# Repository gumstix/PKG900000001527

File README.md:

# Gumstix Raspberry Pi CM4 PoE Smart Camera
# PKG900000001527 ![][thumbnail]

The **Gumstix Raspberry Pi CM4 PoE Smart Camera** carrier board combines Power over Ethernet and Google's Coral AI accelerator chip with the Raspberry Pi CM4 and Raspberry Pi Camera to deliver a fast and powerful image classification, object identification or behavioral inference computer with low latency and single-cable deployment.

__Features Include__:
* Google Coral G313 TPU
* Raspberry Pi Camera connector
* USB Gigabit Ethernet and power via Silvertel Ag9700
* Board to board connectors for the Raspberry Pi CM4

__Links:__
* [AutoDoc Datasheet][autodoc]
* [Specifications][spec]
* [Store Page][store]
* [Schematics and Layout][hardware]

[thumbnail]: about:blank
[autodoc]: PKG900000001527_AutoDoc.pdf
[spec]: PKG900000001527_SpecSheet.pdf
[store]: https://store.gumstix.com/cm4-poe-smart-camera/
[hardware]: hardware/hardware.md
[firmware]: firmware/firmware.md

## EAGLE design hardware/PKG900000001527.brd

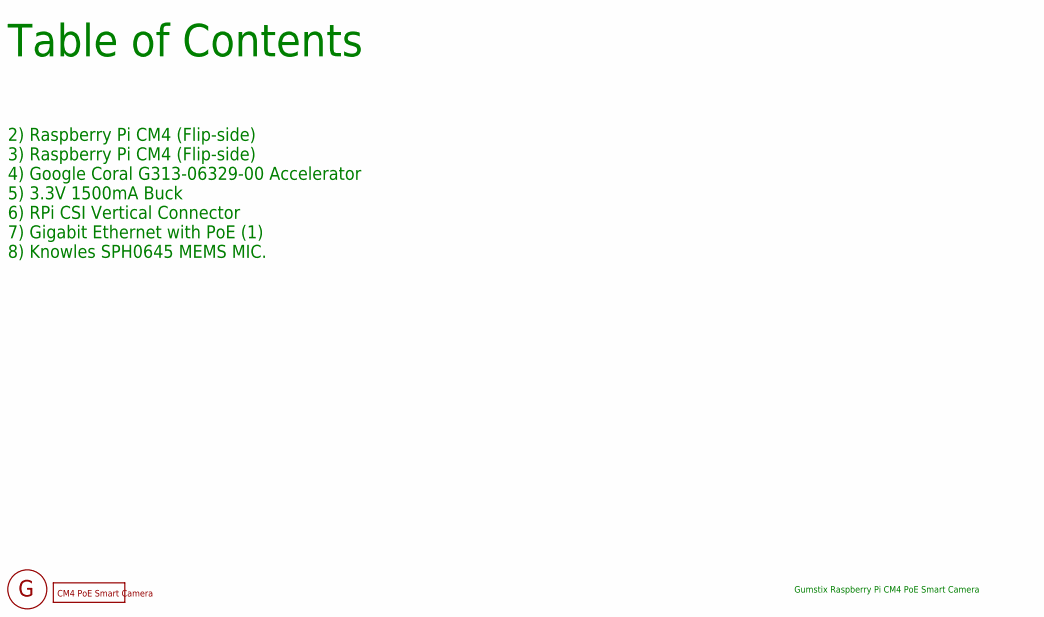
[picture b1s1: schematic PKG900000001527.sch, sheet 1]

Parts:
FD1, FD2, FD3, FD4, FD5, FD6: DNP; FIDUCIAL
U$2: DNP; GEPPETTO_LABEL
U$3: DNP; GEPPETTO_LOGO_SILK10

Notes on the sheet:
Table of Contents
Gumstix Raspberry Pi CM4 PoE Smart Camera
2) Raspberry Pi CM4 (Flip-side)
3) Raspberry Pi CM4 (Flip-side)
4) Google Coral G313-06329-00 Accelerator
5) 3.3V 1500mA Buck
6) RPi CSI Vertical Connector
7) Gigabit Ethernet with PoE (1)
8) Knowles SPH0645 MEMS MIC.

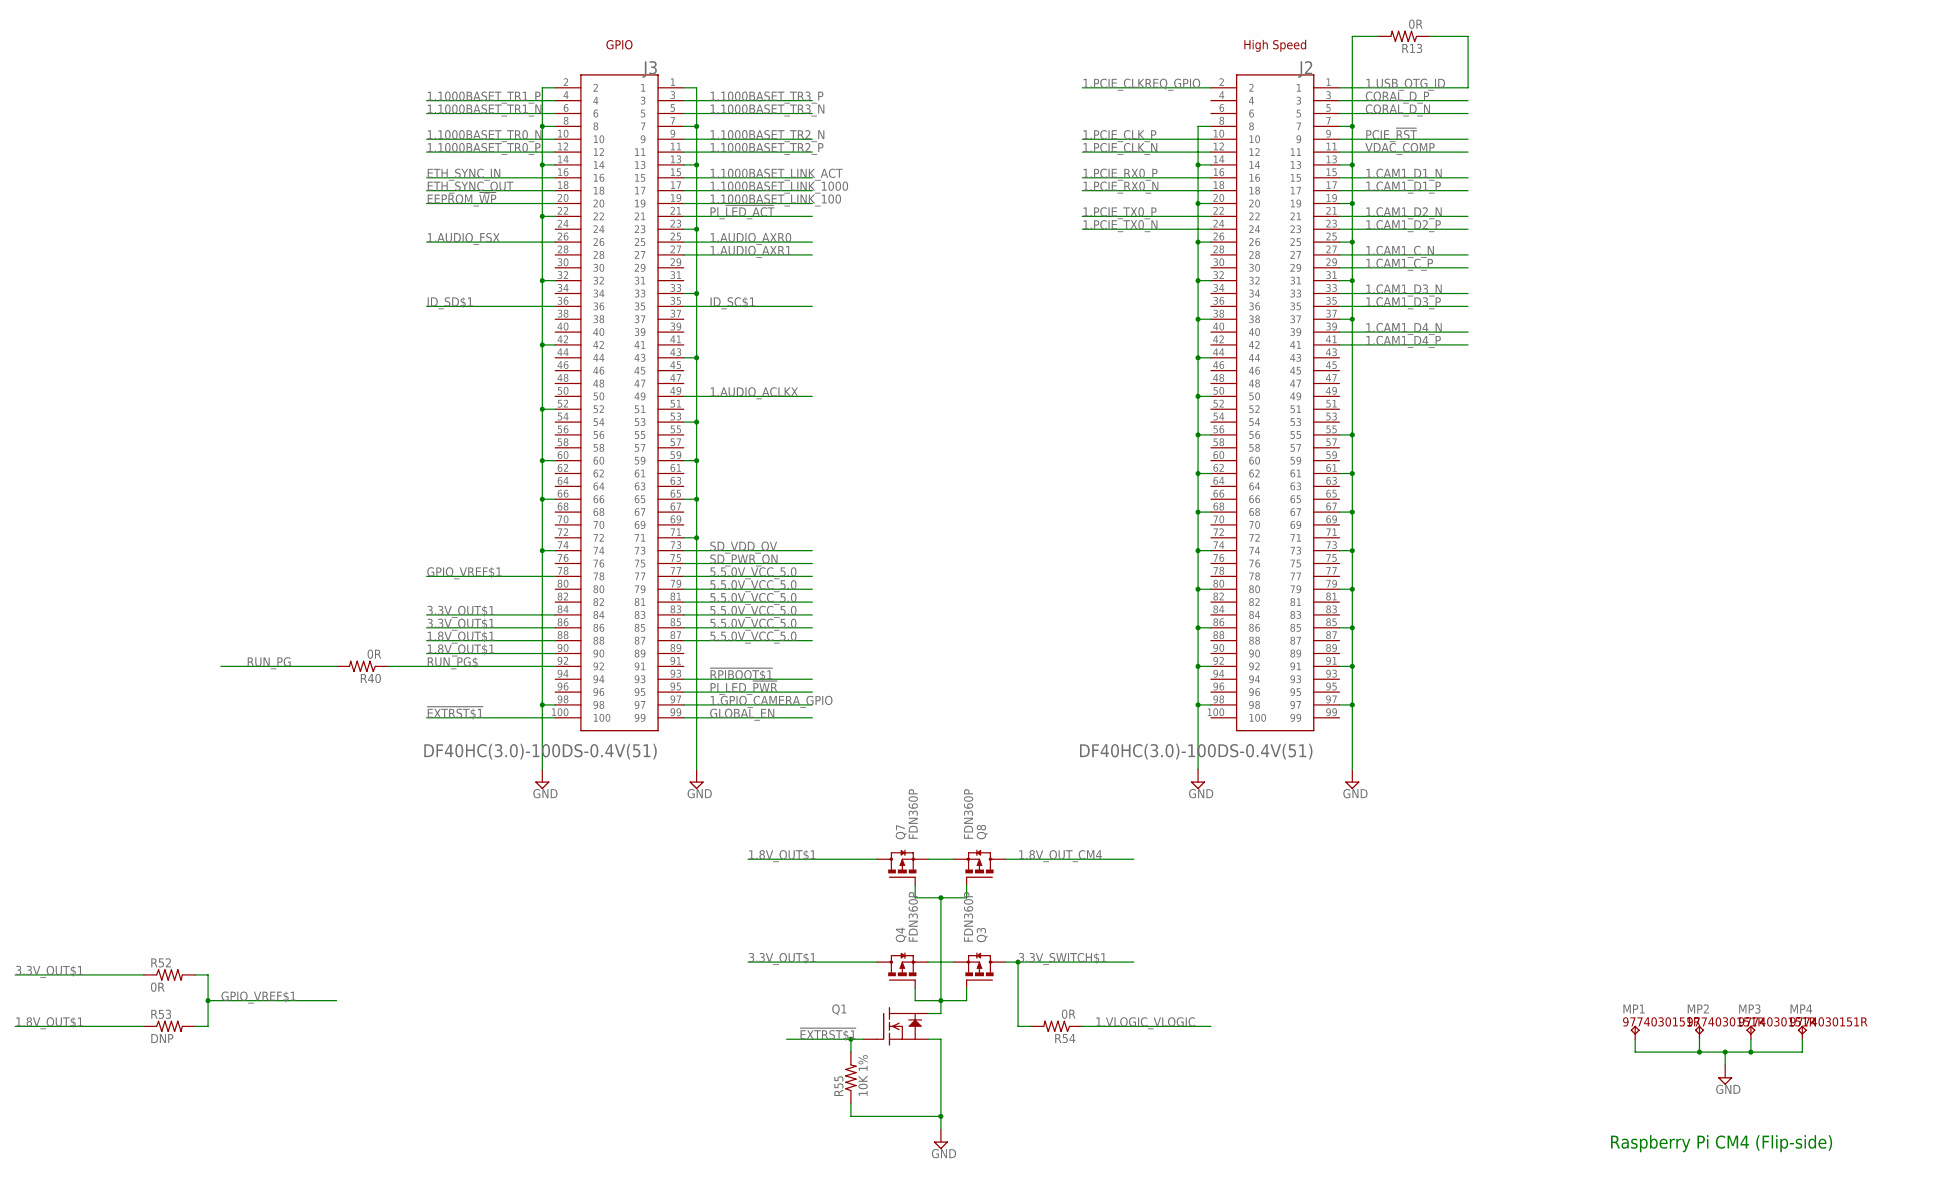
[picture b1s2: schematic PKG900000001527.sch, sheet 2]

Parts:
J2, J3: DF40HC(3.0)-100DS-0.4V(51); HRS_DF40C-100DS-0.4V(51)
MP1, MP2, MP3, MP4: 9774030151R; WA-SMSI_9774___151
Q1: BSS138; SOT23
Q3, Q4, Q7, Q8: FDN360P; SOT23
R13, R40, R52, R54: 0R; 0201
R53: DNP; 0201
R55: 10K 1%; 0201

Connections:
1.8V_OUT$1: J3.88, J3.90, Q7.3 (D), R53.1
1.8V_OUT_CM4: Q8.3 (D); also elsewhere on the board
1.1000BASET_LINK_100: J3.19
1.1000BASET_LINK_1000: J3.17; also elsewhere on the board
1.1000BASET_LINK_ACT: J3.15; also elsewhere on the board
1.1000BASET_TR0_N: J3.10; also elsewhere on the board
1.1000BASET_TR0_P: J3.12; also elsewhere on the board
1.1000BASET_TR1_N: J3.6; also elsewhere on the board
1.1000BASET_TR1_P: J3.4; also elsewhere on the board
1.1000BASET_TR2_N: J3.9; also elsewhere on the board
1.1000BASET_TR2_P: J3.11; also elsewhere on the board
1.1000BASET_TR3_N: J3.5; also elsewhere on the board
1.1000BASET_TR3_P: J3.3; also elsewhere on the board
1.AUDIO_ACLKX: J3.49; also elsewhere on the board
1.AUDIO_AXR0: J3.25
1.AUDIO_AXR1: J3.27; also elsewhere on the board
1.AUDIO_FSX: J3.26; also elsewhere on the board
1.CAM1_C_N: J2.27; also elsewhere on the board
1.CAM1_C_P: J2.29; also elsewhere on the board
1.CAM1_D1_N: J2.15; also elsewhere on the board
1.CAM1_D1_P: J2.17; also elsewhere on the board
1.CAM1_D2_N: J2.21; also elsewhere on the board
1.CAM1_D2_P: J2.23; also elsewhere on the board
1.CAM1_D3_N: J2.33
1.CAM1_D3_P: J2.35
1.CAM1_D4_N: J2.39
1.CAM1_D4_P: J2.41
1.GPIO_CAMERA_GPIO: J3.97; also elsewhere on the board
1.PCIE_CLKREQ_GPIO: J2.2; also elsewhere on the board
1.PCIE_CLK_N: J2.12; also elsewhere on the board
1.PCIE_CLK_P: J2.10; also elsewhere on the board
1.PCIE_RX0_N: J2.18; also elsewhere on the board
1.PCIE_RX0_P: J2.16; also elsewhere on the board
1.PCIE_TX0_N: J2.24; also elsewhere on the board
1.PCIE_TX0_P: J2.22; also elsewhere on the board
1.USB_OTG_ID: J2.1, R13.1
1.VLOGIC_VLOGIC: R54.1; also elsewhere on the board
3.3V_OUT$1: J3.84, J3.86, Q4.3 (D), R52.1
3.3V_SWITCH$1: Q3.3 (D), R54.2
5.5.0V_VCC_5.0: J3.77, J3.79, J3.81, J3.83, J3.85, J3.87; also elsewhere on the board
!EXTRST$1: J3.100, Q1.1 (G), R55.2
!RPIBOOT$1: J3.93; also elsewhere on the board
CORAL_D_N: J2.5; also elsewhere on the board
CORAL_D_P: J2.3; also elsewhere on the board
DS_LOAD$1: Q3.2 (S), Q4.2 (S)
DS_LOAD_1V8$1: Q7.2 (S), Q8.2 (S)
EEPROM_!WP: J3.20
ETH_SYNC_IN: J3.16
ETH_SYNC_OUT: J3.18
GLOBAL_EN: J3.99
GND: J2.7, J2.8, J2.13, J2.14, J2.19, J2.20, J2.25, J2.26, J2.31, J2.32, J2.37, J2.38, J2.44, J2.50, J2.55, J2.56, J2.61, J2.62, J2.67, J2.68, J2.73, J2.74, J2.79, J2.80, J2.85, J2.86, J2.91, J2.92, J2.97, J2.98, J3.1, J3.2, J3.7, J3.8, J3.13, J3.14, J3.22, J3.23, J3.32, J3.33, J3.42, J3.43, J3.52, J3.53, J3.59, J3.60, J3.65, J3.66, J3.71, J3.74, J3.98, MP1.1, MP2.1, MP3.1, MP4.1, Q1.2 (S), R13.2, R55.1; also elsewhere on the board
GPIO_VREF$1: J3.78, R52.2, R53.2; also elsewhere on the board
ID_SC$1: J3.35; also elsewhere on the board
ID_SD$1: J3.36; also elsewhere on the board
LOAD_GATE$1: Q1.3 (D), Q3.1 (G), Q4.1 (G), Q7.1 (G), Q8.1 (G)
PCIE_!RST: J2.9
PI_!LED_ACT: J3.21
PI_LED_!PWR: J3.95
RUN_PG: R40.2; also elsewhere on the board
RUN_PG$: J3.92, R40.1
SD_PWR_ON: J3.75
SD_VDD_OV: J3.73
VDAC_COMP: J2.11

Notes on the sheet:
Raspberry Pi CM4 (Flip-side)
GPIO
High Speed

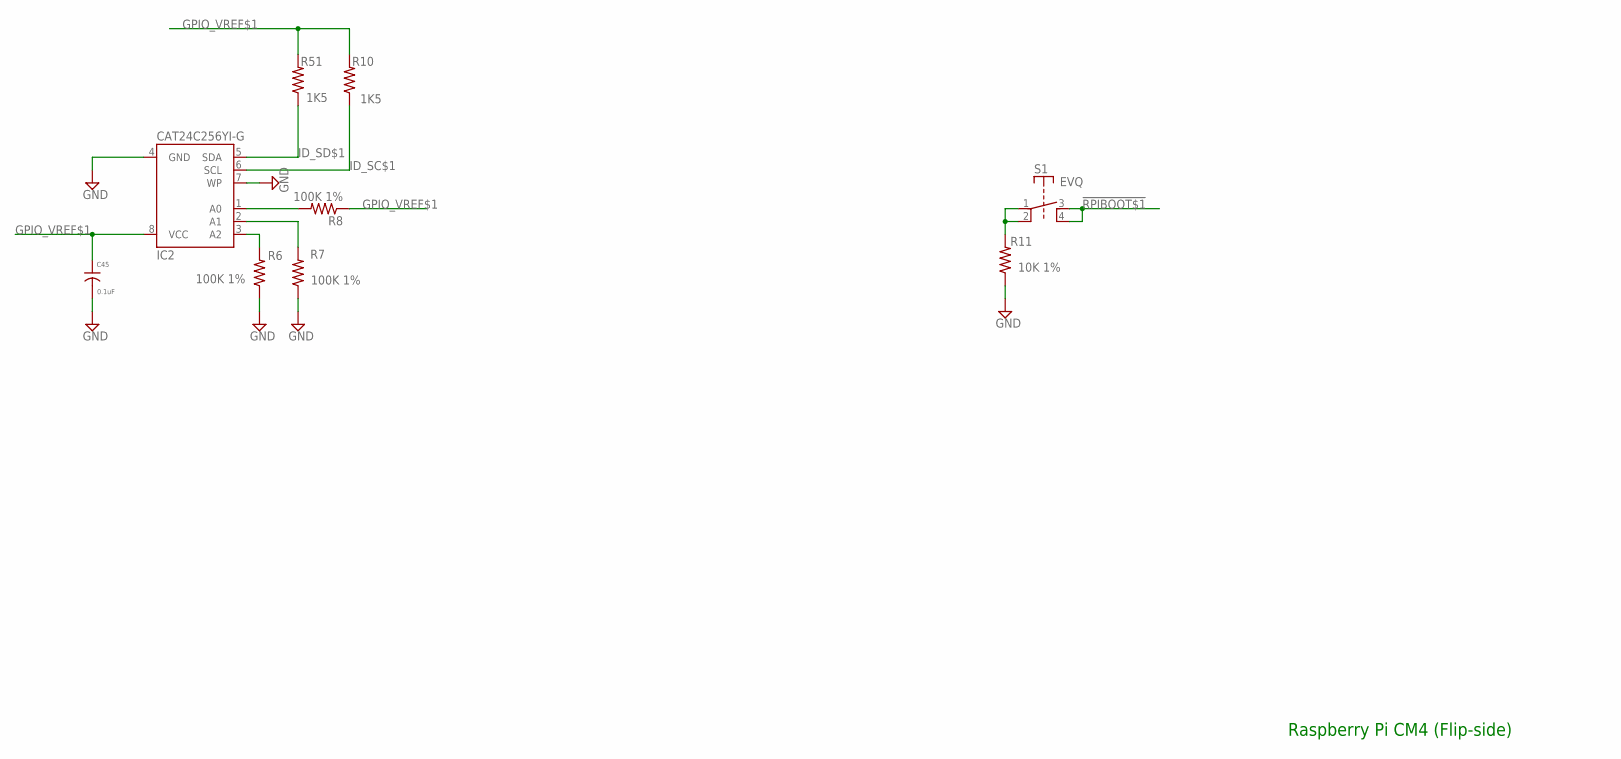
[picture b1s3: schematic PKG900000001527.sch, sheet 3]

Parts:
C45: 0.1uF; 0201
IC2: CAT24C256YI-G; TSSOP8
R6, R7, R8: 100K 1%; 0201
R10, R51: 1K5; 0201
R11: 10K 1%; 0201
S1: EVQ; KMT0

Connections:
!RPIBOOT$1: S1.3 (B), S1.4 (B'); also elsewhere on the board
A0$1: IC2.1 (A0), R8.2
A1$1: IC2.2 (A1), R7.2
A2$1: IC2.3 (A2), R6.2
GND: C45.2, IC2.4 (GND), IC2.7 (WP), R6.1, R7.1, R11.1; also elsewhere on the board
GPIO_VREF$1: C45.1, IC2.8 (VCC), R8.1, R10.2, R51.2; also elsewhere on the board
ID_SC$1: IC2.6 (SCL), R10.1; also elsewhere on the board
ID_SD$1: IC2.5 (SDA), R51.1; also elsewhere on the board
RPIBOOT_SWITCH$1: R11.2, S1.1 (A), S1.2 (A')

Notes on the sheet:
Raspberry Pi CM4 (Flip-side)

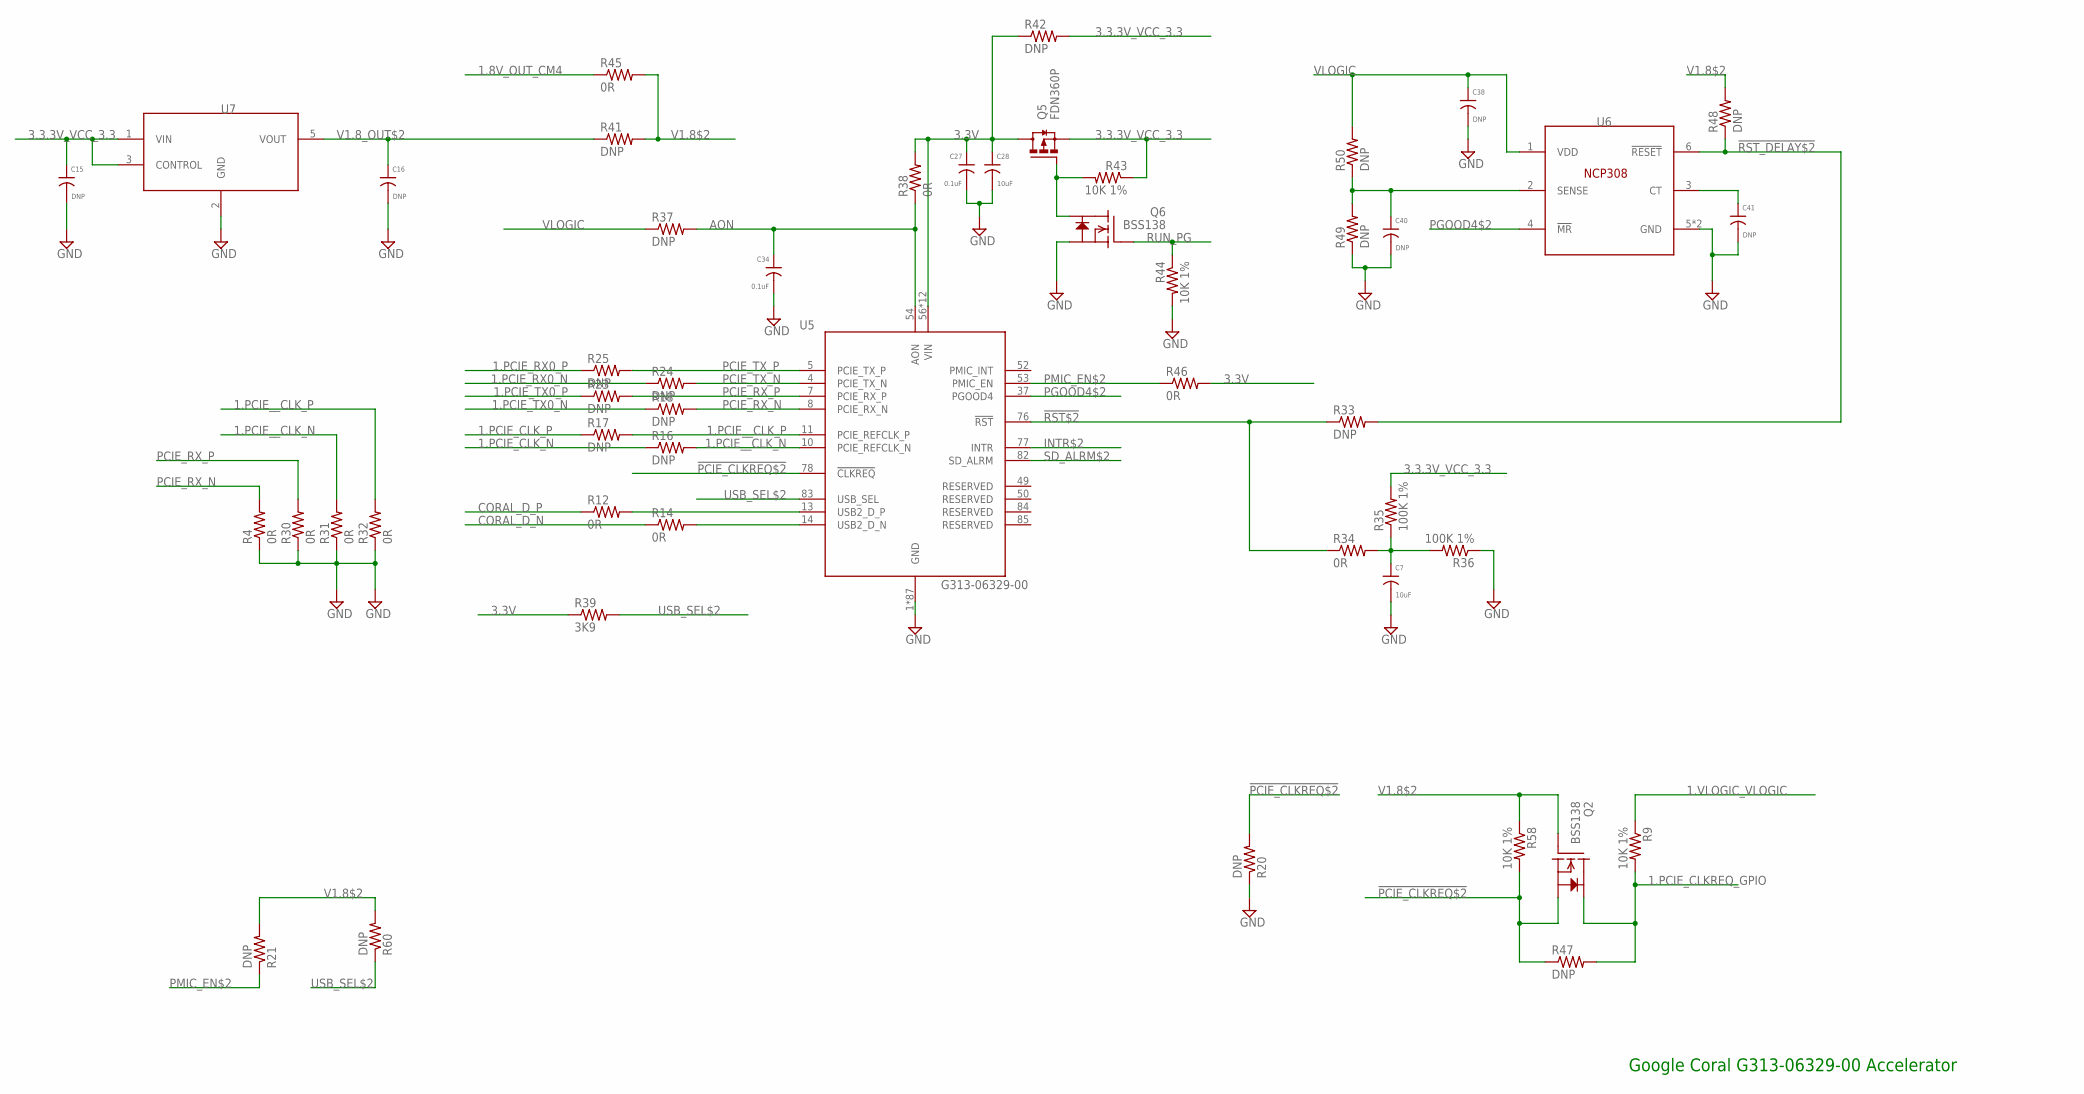
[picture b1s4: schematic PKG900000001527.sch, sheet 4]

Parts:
C7, C28: 10uF; 0603
C15, C38, C40, C41: DNP; 0201
C16: DNP; 0402
C27, C34: 0.1uF; 0201
Q2, Q6: BSS138; SOT23
Q5: FDN360P; SOT23
R4, R12, R14, R30, R31, R32, R34, R38, R46: 0R; 0201
R9, R43, R44, R58: 10K 1%; 0201
R16, R17, R18, R20, R21, R23, R24, R25, R33, R37, R47, R48, R49, R50, R60: DNP; 0201
R35, R36: 100K 1%; 0201
R39: 3K9; 0201
R41: DNP; 0603
R42: DNP; 0805
R45: 0R; 0603
U5: G313-06329-00
U6: DNP; WDFN6
U7: DNP; SOT-23-5

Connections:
1.8V_OUT_CM4: R45.1; also elsewhere on the board
1.PCIE_CLKREQ_GPIO: Q2.3 (D), R9.2, R47.2; also elsewhere on the board
1.PCIE_CLK_N: R16.1; also elsewhere on the board
1.PCIE_CLK_P: R17.1; also elsewhere on the board
1.PCIE_RX0_N: R24.1; also elsewhere on the board
1.PCIE_RX0_P: R25.1; also elsewhere on the board
1.PCIE_TX0_N: R18.1; also elsewhere on the board
1.PCIE_TX0_P: R23.1; also elsewhere on the board
1.PCIE__CLK_N: R16.2, R31.2, U5.10 (PCIE_REFCLK_N)
1.PCIE__CLK_P: R17.2, R32.2, U5.11 (PCIE_REFCLK_P)
1.VLOGIC_VLOGIC: R9.1; also elsewhere on the board
3.3.3V_VCC_3.3: C15.1, Q5.2 (S), R35.2, R42.2, R43.1, U7.1 (VIN), U7.3 (CONTROL); also elsewhere on the board
3.3V: C27.1, C28.1, Q5.3 (D), R38.2, R39.1, R42.1, R46.2, U5.56 (VIN), U5.57 (VIN), U5.58 (VIN), U5.59 (VIN), U5.60 (VIN), U5.61 (VIN), U5.62 (VIN), U5.63 (VIN), U5.64 (VIN), U5.65 (VIN), U5.66 (VIN), U5.67 (VIN)
!PCIE_CLKREQ$2: Q2.2 (S), R20.2, R47.1, R58.2, U5.78 (!CLKREQ)
!RST$2: R33.1, R34.1, U5.76 (!RST)
!RST_DELAY$2: R33.2, R48.1, U6.6 (!RESET)
AON: C34.1, R37.2, R38.1, U5.54 (AON)
CORAL_D_N: R14.1; also elsewhere on the board
CORAL_D_P: R12.1; also elsewhere on the board
CORAL_D__N: R14.2, U5.14 (USB2_D_N)
CORAL_D__P: R12.2, U5.13 (USB2_D_P)
CT1$2: C41.1, U6.3 (CT)
FET_ENABLE: Q5.1 (G), Q6.3 (D), R43.2
GND: C7.2, C15.2, C16.2, C27.2, C28.2, C34.2, C38.2, C40.2, C41.2, Q6.2 (S), R4.1, R20.1, R30.1, R31.1, R32.1, R36.1, R44.2, R49.1, U5.1 (GND), U5.2 (GND), U5.3 (GND), U5.6 (GND), U5.9 (GND), U5.12 (GND), U5.15 (GND), U5.16 (GND), U5.17 (GND), U5.18 (GND), U5.19 (GND), U5.20 (GND), U5.21 (GND), U5.22 (GND), U5.23 (GND), U5.24 (GND), U5.25 (GND), U5.26 (GND), U5.27 (GND), U5.28 (GND), U5.29 (GND), U5.30 (GND), U5.31 (GND), U5.32 (GND), U5.33 (GND), U5.34 (GND), U5.35 (GND), U5.36 (GND), U5.38 (GND), U5.39 (GND), U5.40 (GND), U5.41 (GND), U5.42 (GND), U5.43 (GND), U5.44 (GND), U5.45 (GND), U5.46 (GND), U5.47 (GND), U5.48 (GND), U5.51 (GND), U5.55 (GND), U5.68 (GND), U5.69 (GND), U5.70 (GND), U5.71 (GND), U5.72 (GND), U5.73 (GND), U5.74 (GND), U5.75 (GND), U5.79 (GND), U5.80 (GND), U5.81 (GND), U5.86 (GND), U5.87 (GND), U5.88 (GND), U5.89 (GND), U5.90 (GND), U5.91 (GND), U5.92 (GND), U5.93 (GND), U5.94 (GND), U5.95 (GND), U5.96 (GND), U5.97 (GND), U5.98 (GND), U5.99 (GND), U5.100 (GND), U5.101 (GND), U5.102 (GND), U5.103 (GND), U5.104 (GND), U5.105 (GND), U5.106 (GND), U5.107 (GND), U5.108 (GND), U5.109 (GND), U5.110 (GND), U5.111 (GND), U5.112 (GND), U5.113 (GND), U5.114 (GND), U5.115 (GND), U5.116 (GND), U5.117 (GND), U5.118 (GND), U5.119 (GND), U5.120 (GND), U6.5 (GND), U6.EPAD (GND), U7.2 (GND); also elsewhere on the board
INTR$2: U5.77 (INTR)
PCIE_RX_N: R4.2, R18.2, U5.8 (PCIE_RX_N)
PCIE_RX_P: R23.2, R30.2, U5.7 (PCIE_RX_P)
PCIE_TX_N: R24.2, U5.4 (PCIE_TX_N)
PCIE_TX_P: R25.2, U5.5 (PCIE_TX_P)
PGOOD4$2: U5.37 (PGOOD4), U6.4 (!MR)
PMIC_EN$2: R21.1, R46.1, U5.53 (PMIC_EN)
RST_RC$: C7.1, R34.2, R35.1, R36.2
RUN_PG: Q6.1 (G), R44.1; also elsewhere on the board
SD_ALRM$2: U5.82 (SD_ALRM)
SENSE$2: C40.1, R49.2, R50.1, U6.2 (SENSE)
USB_SEL$2: R39.2, R60.1, U5.83 (USB_SEL)
V1.8$2: Q2.1 (G), R21.2, R41.2, R45.2, R48.2, R58.1, R60.2
V1.8_OUT$2: C16.1, R41.1, U7.5 (VOUT)
VLOGIC: C38.1, R37.1, R50.2, U6.1 (VDD)

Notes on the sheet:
Google Coral G313-06329-00 Accelerator

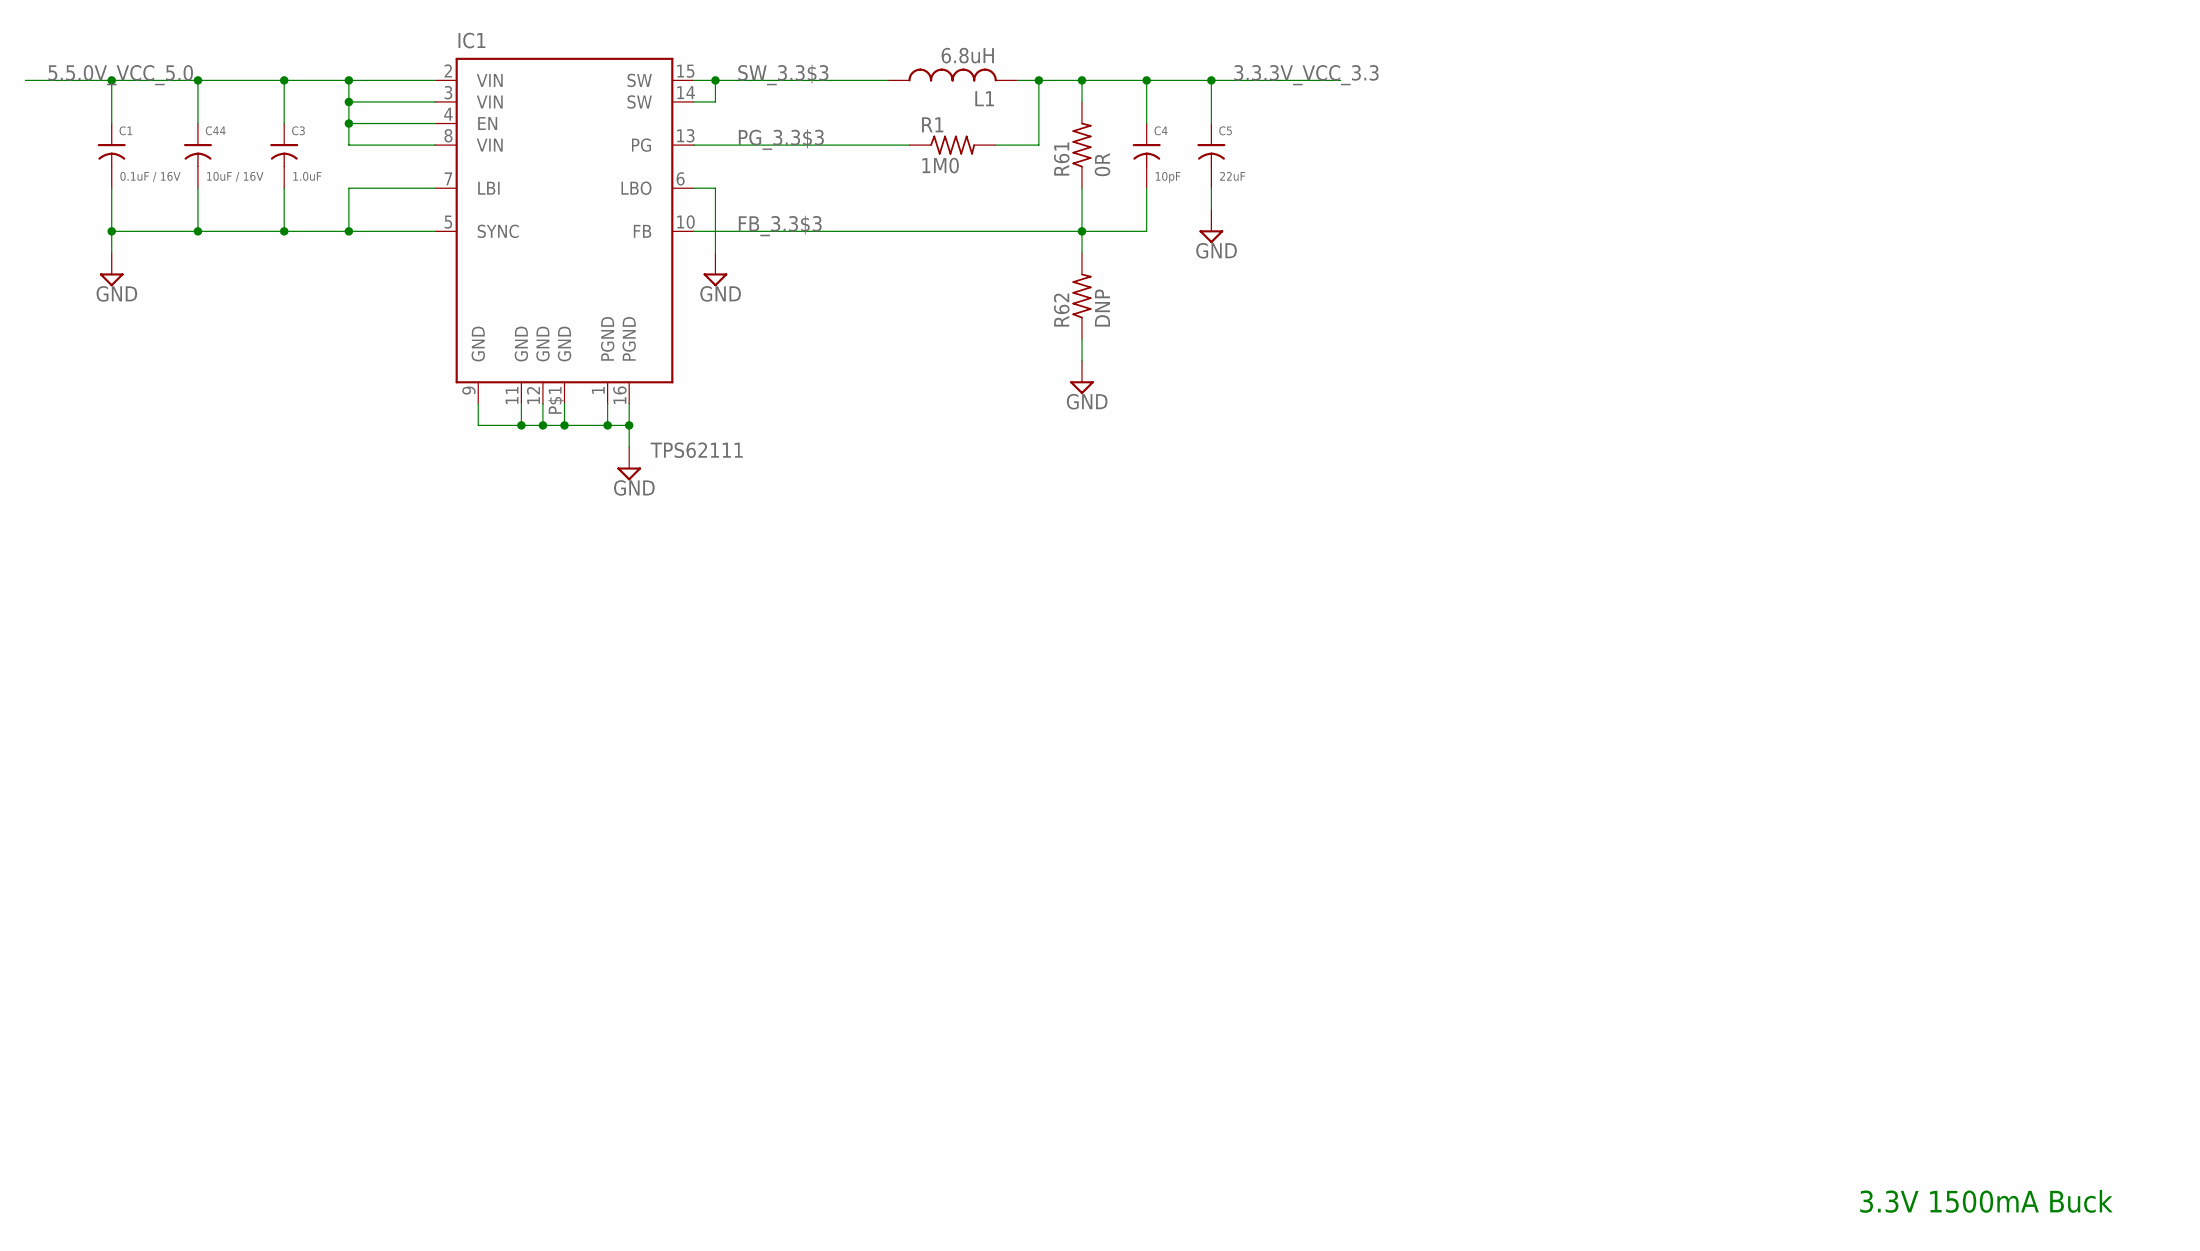
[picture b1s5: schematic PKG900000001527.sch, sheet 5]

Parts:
C1: 0.1uF / 16V; 0402
C3: 1.0uF; 0402
C4: 10pF; 0201
C5: 22uF; 0805
C44: 10uF / 16V; 0805
IC1: TPS62111; PQFP16
L1: 6.8uH; 1515
R1: 1M0; 0201
R61: 0R; 0402
R62: DNP; 0402

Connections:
3.3.3V_VCC_3.3: C4.1, C5.1, L1.2, R1.2, R61.2; also elsewhere on the board
5.5.0V_VCC_5.0: C1.1, C3.1, C44.1, IC1.2 (VIN), IC1.3 (VIN), IC1.4 (EN), IC1.8 (VIN); also elsewhere on the board
FB_3.3$3: C4.2, IC1.10 (FB), R61.1, R62.2
GND: C1.2, C3.2, C5.2, C44.2, IC1.1 (PGND), IC1.5 (SYNC), IC1.6 (LBO), IC1.7 (LBI), IC1.9 (GND), IC1.11 (GND), IC1.12 (GND), IC1.16 (PGND), IC1.P$1 (GND), R62.1; also elsewhere on the board
PG_3.3$3: IC1.13 (PG), R1.1
SW_3.3$3: IC1.14 (SW), IC1.15 (SW), L1.1

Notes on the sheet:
3.3V 1500mA Buck

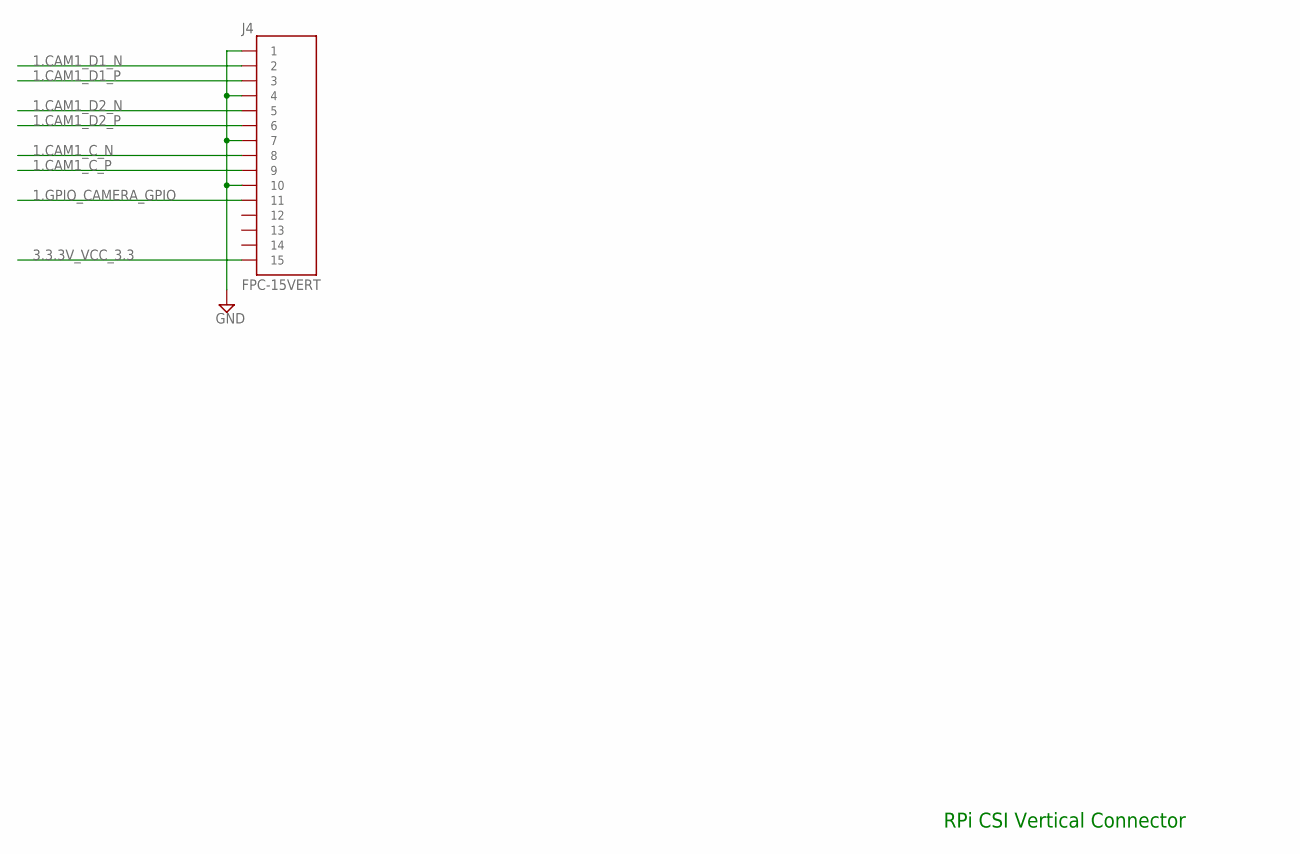
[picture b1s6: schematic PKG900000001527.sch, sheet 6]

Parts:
J4: FPC-15VERT; 1-1734248-5

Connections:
1.CAM1_C_N: J4.1_8 (8); also elsewhere on the board
1.CAM1_C_P: J4.1_9 (9); also elsewhere on the board
1.CAM1_D1_N: J4.1_2 (2); also elsewhere on the board
1.CAM1_D1_P: J4.1_3 (3); also elsewhere on the board
1.CAM1_D2_N: J4.1_5 (5); also elsewhere on the board
1.CAM1_D2_P: J4.1_6 (6); also elsewhere on the board
1.GPIO_CAMERA_GPIO: J4.1_11 (11); also elsewhere on the board
3.3.3V_VCC_3.3: J4.1_15 (15); also elsewhere on the board
GND: J4.1_1 (1), J4.1_4 (4), J4.1_7 (7), J4.1_10 (10); also elsewhere on the board

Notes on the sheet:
RPi CSI Vertical Connector

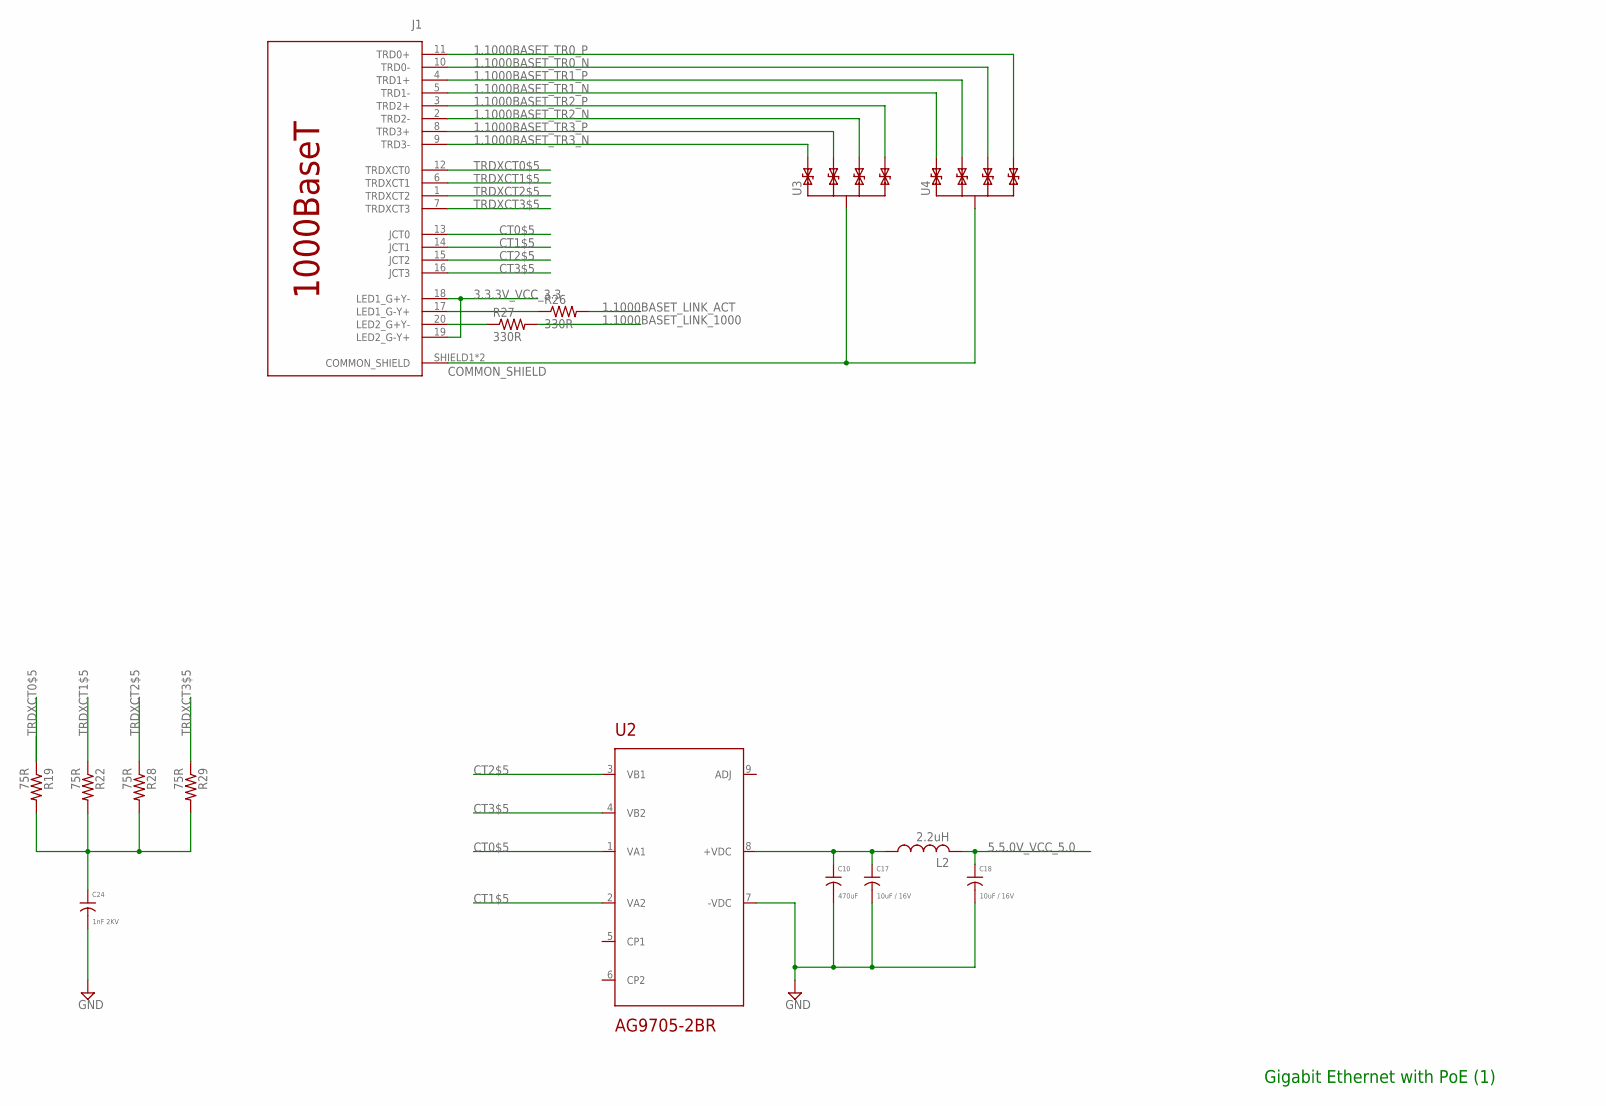
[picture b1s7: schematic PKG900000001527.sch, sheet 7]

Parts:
C10: 470uF; PANASONIC_F
C17, C18: 10uF / 16V; 0805
C24: 1nF 2KV; 1206
J1: 1000BASET_POE; 7499511440
L2: 2.2uH; 1515
R19, R22, R28, R29: 75R; 0402
R26, R27: 330R; 0402
U2: AG9705-2BR; AG9700
U3, U4: TPD4E02B0410-USON; UFDFN-10

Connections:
1.1000BASET_LINK_1000: R27.2; also elsewhere on the board
1.1000BASET_LINK_ACT: R26.2; also elsewhere on the board
1.1000BASET_TR0_N: J1.10 (TRD0-), U4.4 (P3), U4.7 (P3); also elsewhere on the board
1.1000BASET_TR0_P: J1.11 (TRD0+), U4.5 (P4), U4.6 (P4); also elsewhere on the board
1.1000BASET_TR1_N: J1.5 (TRD1-), U4.1, U4.10 (P1); also elsewhere on the board
1.1000BASET_TR1_P: J1.4 (TRD1+), U4.2, U4.9 (P2); also elsewhere on the board
1.1000BASET_TR2_N: J1.2 (TRD2-), U3.4 (P3), U3.7 (P3); also elsewhere on the board
1.1000BASET_TR2_P: J1.3 (TRD2+), U3.5 (P4), U3.6 (P4); also elsewhere on the board
1.1000BASET_TR3_N: J1.9 (TRD3-), U3.1, U3.10 (P1); also elsewhere on the board
1.1000BASET_TR3_P: J1.8 (TRD3+), U3.2, U3.9 (P2); also elsewhere on the board
3.3.3V_VCC_3.3: J1.18 (LED1_G+Y-), J1.19 (LED2_G-Y+); also elsewhere on the board
5.5.0V_VCC_5.0: C18.1, L2.2; also elsewhere on the board
COMMON_SHIELD: J1.SHIELD1 (COMMON_SHIELD), J1.SHIELD2 (COMMON_SHIELD), U3.3 (SHIELD), U3.8 (SHIELD), U4.3 (SHIELD), U4.8 (SHIELD)
CT0$5: J1.13 (JCT0), U2.1 (VA1)
CT1$5: J1.14 (JCT1), U2.2 (VA2)
CT2$5: J1.15 (JCT2), U2.3 (VB1)
CT3$5: J1.16 (JCT3), U2.4 (VB2)
GND: C10.- (2), C17.2, C18.2, C24.2, U2.7 (-VDC); also elsewhere on the board
MFA0_R$5: J1.20 (LED2_G+Y-), R27.1
MFA1_R$5: J1.17 (LED1_G-Y+), R26.1
TRDXCT0$5: J1.12 (TRDXCT0), R19.1
TRDXCT1$5: J1.6 (TRDXCT1), R22.1
TRDXCT2$5: J1.1 (TRDXCT2), R28.1
TRDXCT3$5: J1.7 (TRDXCT3), R29.1
TRDXCT_COMMON$5: C24.1, R19.2, R22.2, R28.2, R29.2
V3.3_UNFILT$5: C10.+ (1), C17.1, L2.1, U2.8 (+VDC)

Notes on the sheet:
Gigabit Ethernet with PoE (1)

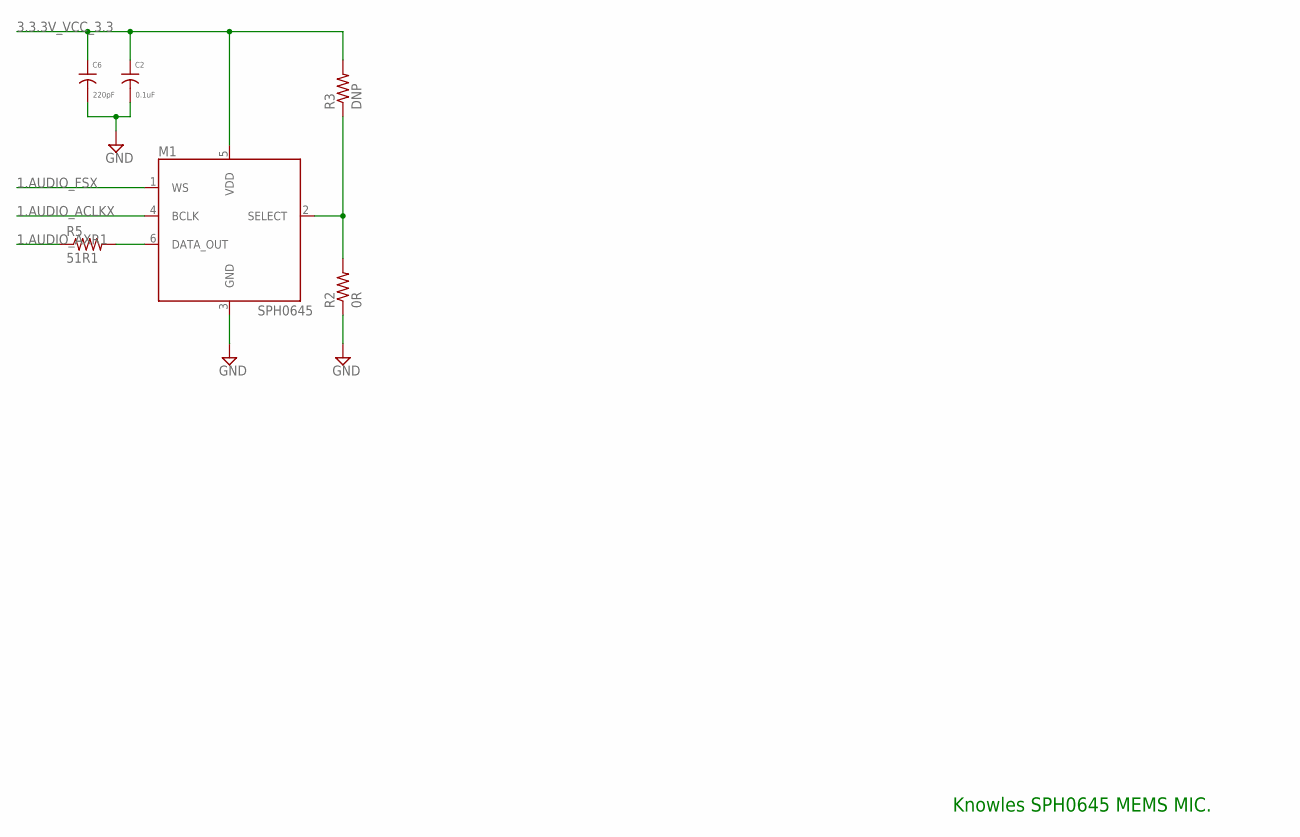
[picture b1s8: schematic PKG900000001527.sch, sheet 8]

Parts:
C2: 0.1uF; 0201
C6: 220pF; 0201
M1: SPH0645
R2: 0R; 0201
R3: DNP; 0201
R5: 51R1; 0402

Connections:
1.AUDIO_ACLKX: M1.4 (BCLK); also elsewhere on the board
1.AUDIO_AXR1: R5.1; also elsewhere on the board
1.AUDIO_FSX: M1.1 (WS); also elsewhere on the board
3.3.3V_VCC_3.3: C2.1, C6.1, M1.5 (VDD), R3.2; also elsewhere on the board
GND: C2.2, C6.2, M1.3 (GND), R2.1; also elsewhere on the board
SDI$7: M1.6 (DATA_OUT), R5.2
SELECT$7: M1.2 (SELECT), R2.2, R3.1

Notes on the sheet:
Knowles SPH0645 MEMS MIC.

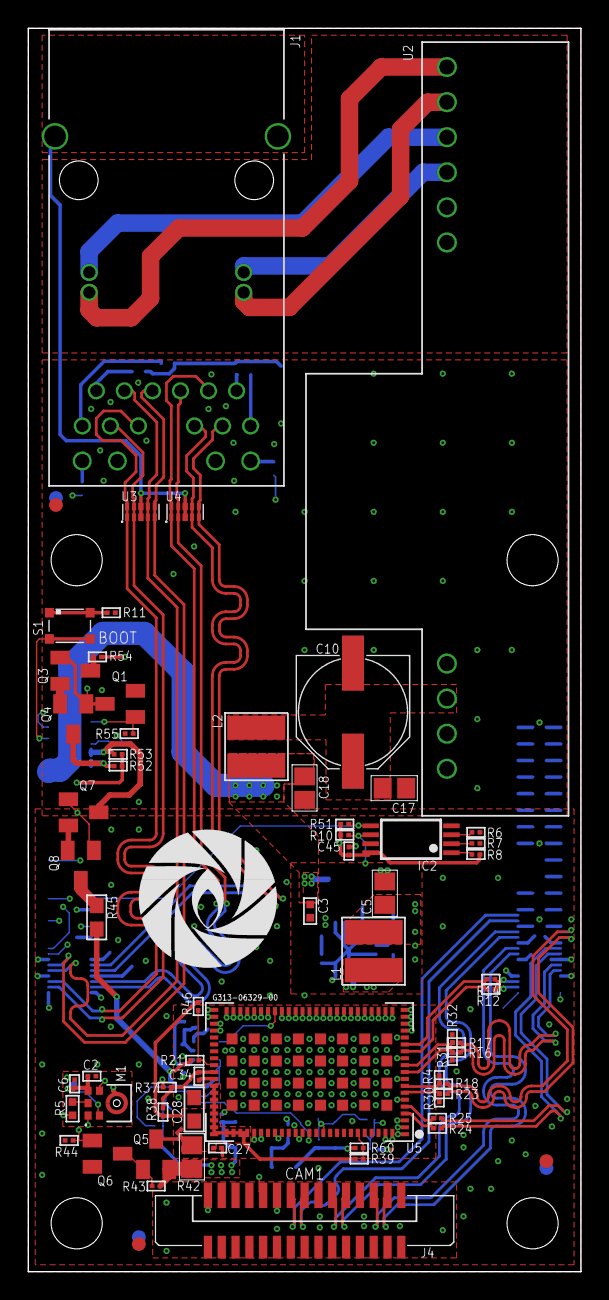
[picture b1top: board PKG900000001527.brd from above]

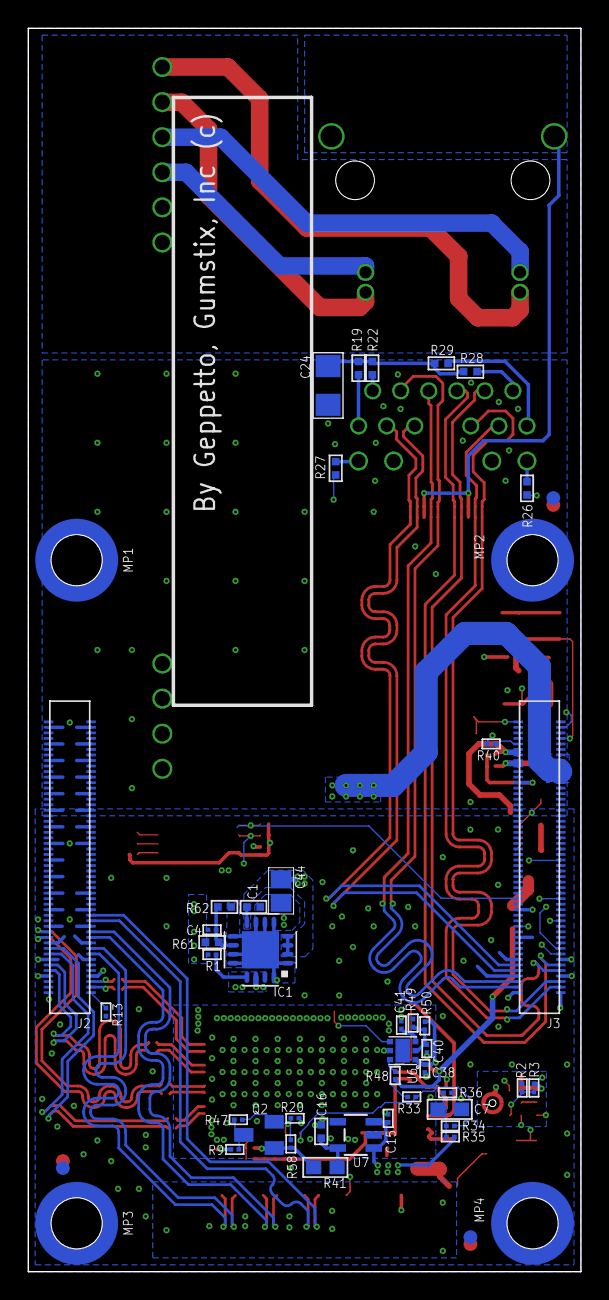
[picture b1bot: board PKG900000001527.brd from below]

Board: 6 copper layers, 40.0 x 90.0 mm, 115 parts (49 on the bottom side), 93 nets.

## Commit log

2020-10-14 Add autodoc, readme content and file structure
2020-10-15 Added hardware documents for revision 1.
2020-10-15 add links to sch and brd
2020-10-19 Update firmware image to Ubuntu 20.04 CM4 image.
2020-11-23 Update firmware.md
    Add image username and password information.

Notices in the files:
parts and their libraries:
qualified_1: COMPANY_AND_YEAR: Geppetto, Gumstix Inc (c) 2019
